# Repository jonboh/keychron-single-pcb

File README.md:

These single key pcbs can be used to make a dactyl based on keychron switches.

The footprints of the pcb come from the [keyboard design](https://github.com/girishji/keychron-optical-keyboard) by girish.
See his [blog post](https://girishji.github.io/2022/08/17/optical-keyboard-design.html) for more details on how to design your keyboard.

I did some tests with these pcbs, but I didn't
end up building the whole keyboard. If you want to experiment with these pcbs make sure to
have a hot air gun to do the SMD soldering of the IR and PT.

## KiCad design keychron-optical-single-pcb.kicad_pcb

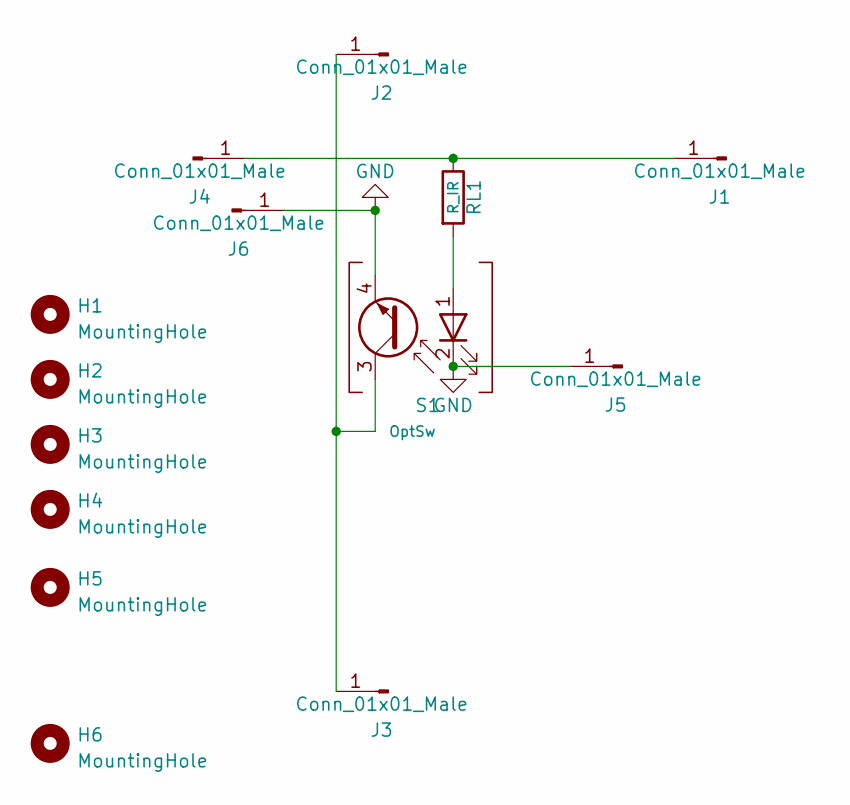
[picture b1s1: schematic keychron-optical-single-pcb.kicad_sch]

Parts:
H1, H2, H3, H4, H5, H6: MountingHole; MountingHole_1.2mm_M1
J1, J2, J3, J4, J5, J6: Conn_01x01_Male; TestPoint_THTPad_1.0x2.5mm_Drill0.5mm
RL1: R_IR; R_0805_2012Metric_Pad1.20x1.40mm_HandSolder; JLC 0603-1608
S1: OptSw; Keychron_Optical_Switch_1u

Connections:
GND: J5.1, J6.1, S1.2 (IR_K), S1.4 (E)
unnamed: J1.1, J4.1, RL1.1
unnamed: J2.1, J3.1, S1.3 (C)
unnamed: RL1.2, S1.1 (IR_A)

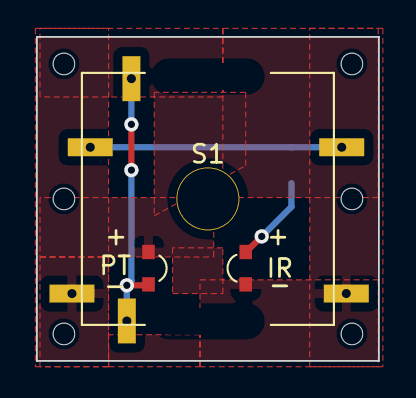
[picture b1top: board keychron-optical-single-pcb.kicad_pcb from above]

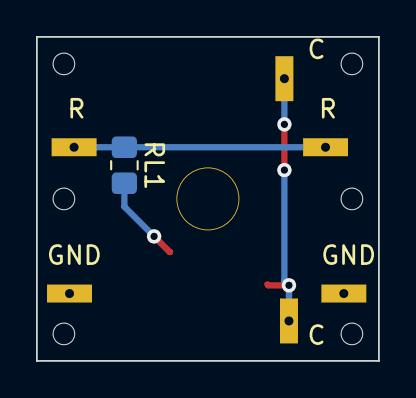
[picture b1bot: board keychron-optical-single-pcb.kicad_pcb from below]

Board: 2 copper layers, 19.0 x 18.0 mm, 14 parts (2 on the bottom side), 4 nets.

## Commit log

2023-11-04 archive
2023-11-04 add minimar readme
2023-11-04 add captures
2023-11-04 add some warnings
2023-11-04 Create LICENSE
